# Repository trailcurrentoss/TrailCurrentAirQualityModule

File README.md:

# TrailCurrent Air Quality Module

Air quality sensor module for monitoring environmental conditions including temperature, humidity, and air quality metrics. Part of the [TrailCurrent](https://trailcurrent.com) open-source vehicle platform.

## Hardware Overview

- **Function:** Environmental monitoring module combining temperature, humidity, and air quality sensing
- **Key Features:**
  - DHT22 temperature and humidity sensor
  - Air quality sensing capability
  - Compact design suitable for integration into larger systems
  - PlatformIO-based firmware for configuration and operation

## Hardware Requirements

### Components

- **Sensors:**
  - DHT22 temperature/humidity sensor
  - Air quality sensor module

- **Connectors:**
  - JST XH 4-pin connectors for power and signal distribution

### KiCAD Library Dependencies

This project uses the consolidated [TrailCurrentKiCADLibraries](https://github.com/trailcurrentoss/TrailCurrentKiCADLibraries).

**Setup:**

```bash
# Clone the library
git clone git@github.com:trailcurrentoss/TrailCurrentKiCADLibraries.git

# Set environment variables (add to ~/.bashrc or ~/.zshrc)
export TRAILCURRENT_SYMBOL_DIR="/path/to/TrailCurrentKiCADLibraries/symbols"
export TRAILCURRENT_FOOTPRINT_DIR="/path/to/TrailCurrentKiCADLibraries/footprints"
export TRAILCURRENT_3DMODEL_DIR="/path/to/TrailCurrentKiCADLibraries/3d_models"
```

See [KICAD_ENVIRONMENT_SETUP.md](https://github.com/trailcurrentoss/TrailCurrentKiCADLibraries/blob/main/KICAD_ENVIRONMENT_SETUP.md) in the library repository for detailed setup instructions.

## Opening the Project

1. **Set up environment variables** (see Library Dependencies above)
2. **Open KiCAD:**
   ```bash
   kicad /path/to/EDA/TrailCurrentAirQualityModule/TrailCurrentAirQualityModule.kicad_pro
   ```
3. **Verify libraries load** - All symbol and footprint libraries should resolve without errors
4. **View 3D models** - Open PCB and press `Alt+3` to view the 3D visualization
   - All 3D models should load from the consolidated library path
   - Models use relative `${TRAILCURRENT_3DMODEL_DIR}` references

## Firmware

See `src/` directory for PlatformIO-based firmware.

**Setup:**
```bash
# Install PlatformIO (if not already installed)
pip install platformio

# Build firmware
pio run -d /path/to/project

# Upload to board
pio run -t upload -d /path/to/project
```

### Firmware Dependencies

This firmware depends on the following public libraries:

- **[C6SuperMiniRgbLedLibrary](https://github.com/trailcurrentoss/C6SuperMiniRgbLedLibrary)** (v0.0.1) - RGB LED status indicator driver
- **[Esp32C6OtaUpdateLibrary](https://github.com/trailcurrentoss/Esp32C6OtaUpdateLibrary)** (v0.0.1) - Over-the-air firmware update functionality
- **[Esp32C6TwaiTaskBasedLibrary](https://github.com/trailcurrentoss/Esp32C6TwaiTaskBasedLibrary)** (v0.0.3) - CAN bus communication interface
- **[Adafruit DHT sensor library](https://github.com/adafruit/DHT-sensor-library)** (v1.4.6+) - Temperature and humidity sensor

All dependencies are automatically resolved by PlatformIO during the build process.

**WiFi Credentials:**
- Firmware receives WiFi credentials via CAN Bus (ID 0x01) from the TrailCurrent system
- For standalone development/testing without the TrailCurrent system, create a `secrets.h` file in `src/`:
  ```cpp
  // Copy to src/secrets.h for local development only
  // NEVER commit this file - it's in .gitignore
  const char* ssid = "YOUR_SSID_HERE";
  const char* password = "YOUR_PASSWORD_HERE";
  ```

**Future Enhancement:** WiFi credential configuration will be fully implemented via CAN Bus protocol, allowing credentials to be distributed from the TrailCurrent system without firmware modifications.

## Manufacturing

- **PCB Files:** Ready for fabrication via standard PCB services (JLCPCB, OSH Park, etc.)
- **BOM Generation:** Export BOM from KiCAD schematic (Tools → Generate BOM)
- **JLCPCB Assembly:** This project supports automated assembly using JLCPCB
  - See [BOM_ASSEMBLY_WORKFLOW.md](https://github.com/trailcurrentoss/TrailCurrentKiCADLibraries/blob/main/BOM_ASSEMBLY_WORKFLOW.md) for detailed assembly workflow
  - Component library includes LCSC, Mouser, and DigiKey part numbers for flexible sourcing

## Documentation

- **Schematic:** EDA/TrailCurrentAirQualityModule/TrailCurrentAirQualityModule.kicad_sch
- **PCB Layout:** EDA/TrailCurrentAirQualityModule/TrailCurrentAirQualityModule.kicad_pcb

## License

MIT License - See LICENSE file for details

This is open source hardware. You are free to use, modify, and distribute these designs for personal or commercial purposes.

## Contributing

Improvements and contributions are welcome! Please submit issues or pull requests to the main repository.

## Support

For questions about:
- **KiCAD setup:** See [KICAD_ENVIRONMENT_SETUP.md](https://github.com/trailcurrentoss/TrailCurrentKiCADLibraries/blob/main/KICAD_ENVIRONMENT_SETUP.md)
- **Library consolidation:** See [CONNECTOR_CONSOLIDATION_SUMMARY.md](https://github.com/trailcurrentoss/TrailCurrentKiCADLibraries/blob/main/CONNECTOR_CONSOLIDATION_SUMMARY.md)
- **Assembly workflow:** See [BOM_ASSEMBLY_WORKFLOW.md](https://github.com/trailcurrentoss/TrailCurrentKiCADLibraries/blob/main/BOM_ASSEMBLY_WORKFLOW.md)

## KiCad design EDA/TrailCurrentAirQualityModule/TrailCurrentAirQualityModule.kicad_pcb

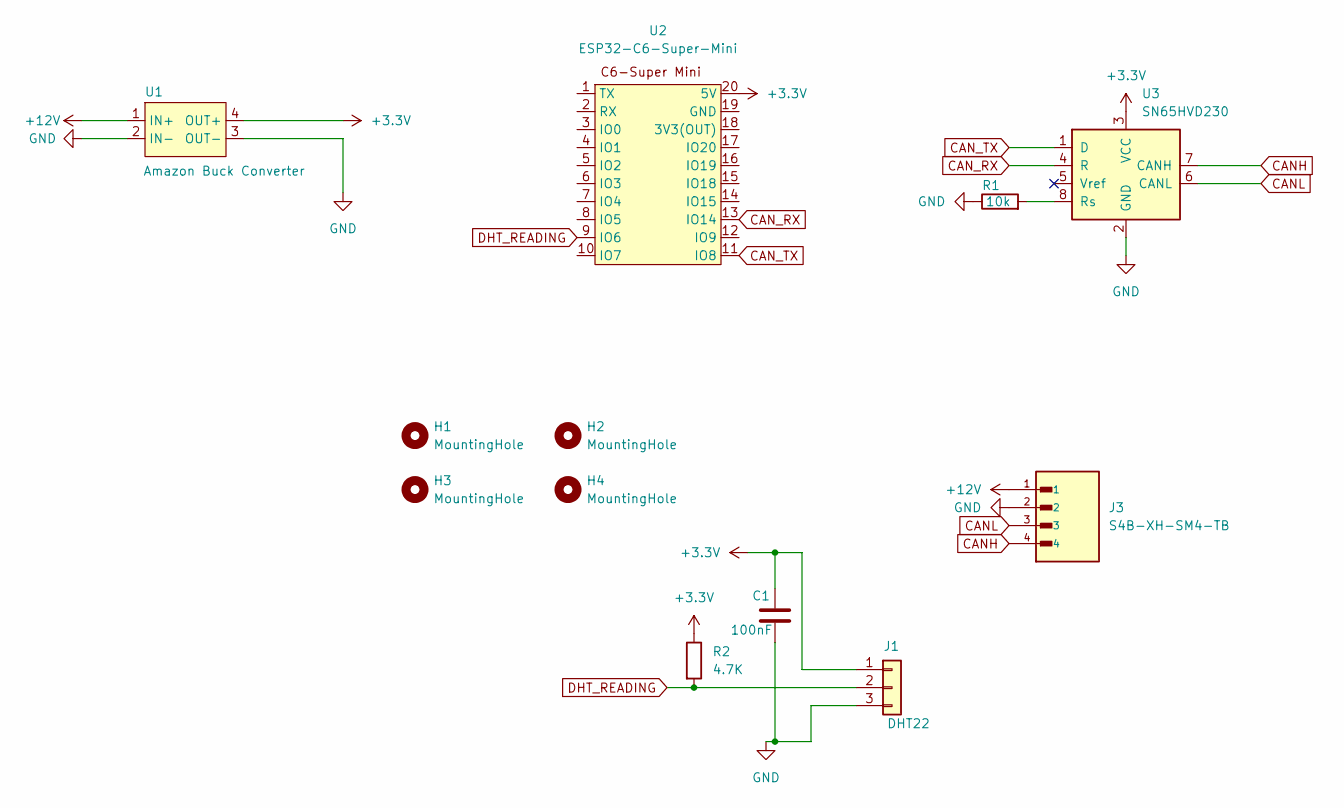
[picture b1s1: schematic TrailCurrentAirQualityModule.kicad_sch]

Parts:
C1: 100nF; C_1206_3216Metric_Pad1.33x1.80mm_HandSolder
H1, H2, H3, H4: MountingHole; MountingHole_2.5mm
J1: DHT22; DHT22_Module
J3: S4B-XH-SM4-TB; JST_S4B-XH-SM4-TB; PARTREV NA; LCSC C161861
R1: 10k; R_1206_3216Metric_Pad1.30x1.75mm_HandSolder
R2: 4.7K; C_1206_3216Metric_Pad1.33x1.80mm_HandSolder
U1: Amazon Buck Converter; AmazonBuckConverter
U2: ESP32-C6-Super-Mini
U3: SN65HVD230; SOIC-8_3.9x4.9mm_P1.27mm

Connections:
+3.3V: C1.1, J1.1, R2.1, U1.4 (OUT+), U2.20 (5V), U3.3 (VCC)
+12V: J3.1, U1.1 (IN+)
CANH: J3.4, U3.7 (CANH)
CANL: J3.3, U3.6 (CANL)
CAN_RX: U2.13 (IO14), U3.4 (R)
CAN_TX: U2.11 (IO8), U3.1 (D)
DHT_READING: J1.2, R2.2, U2.9 (IO6)
GND: C1.2, J1.3, J3.2, R1.1, U1.2 (IN-), U1.3 (OUT-), U3.2 (GND)
unnamed: R1.2, U3.8 (Rs)

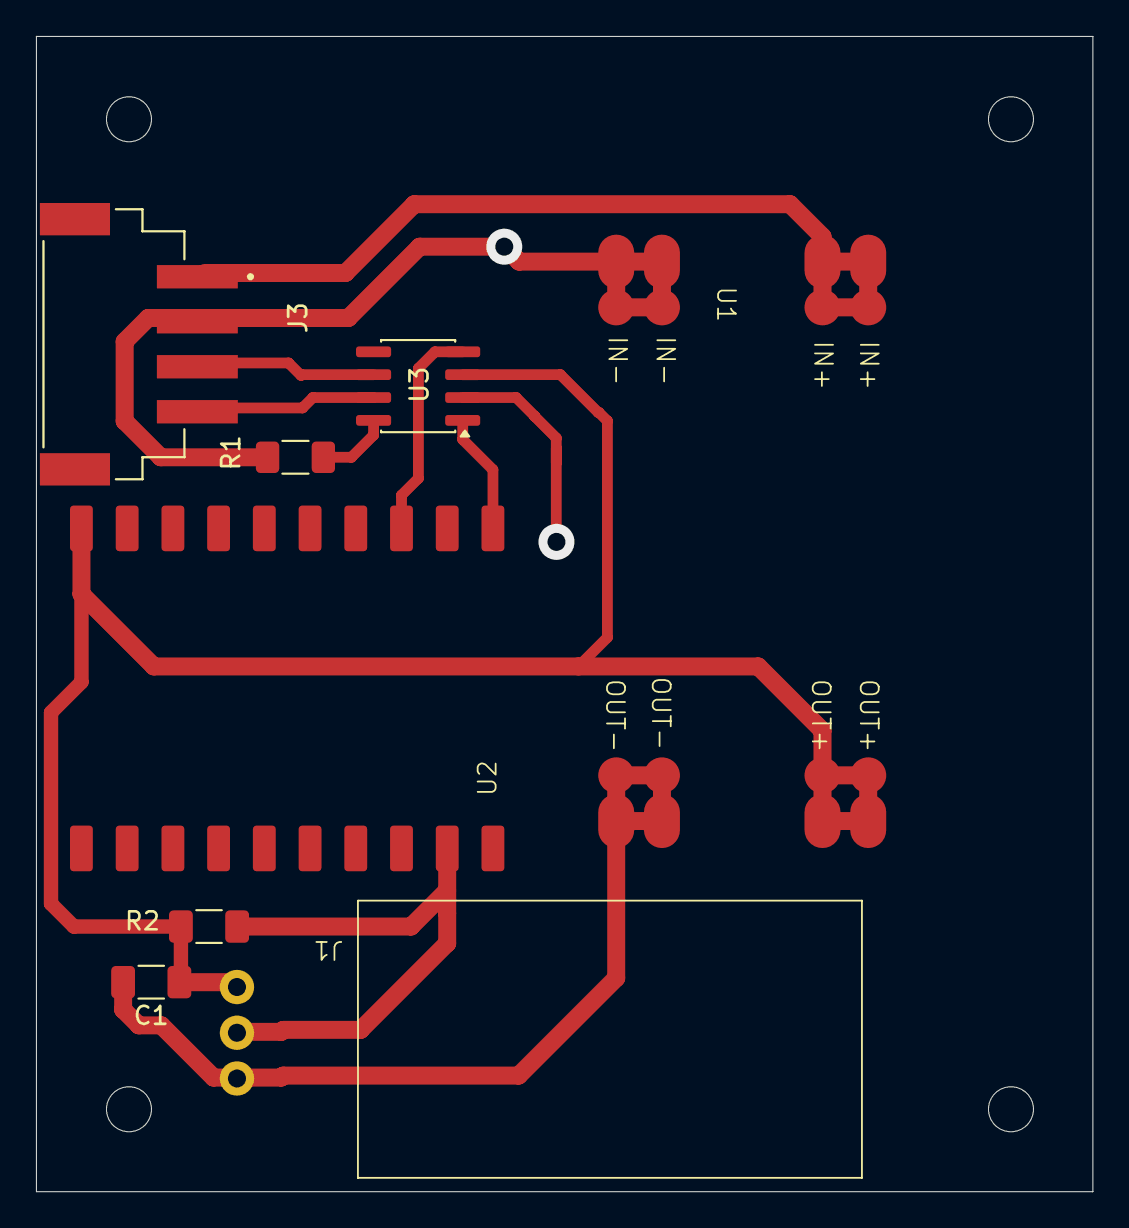
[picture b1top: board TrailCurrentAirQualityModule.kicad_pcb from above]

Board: 2 copper layers, 58.7 x 64.2 mm, 12 parts (0 on the bottom side), 9 nets.

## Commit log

2026-02-12 Initial commit: Clean migration to public Codeberg repository
    This is a fresh start on Codeberg with all security and configuration
    issues addressed:
    Security fixes:
    - Removed all git history (fresh start)
    - No personal paths or credentials exposed
    - All WiFi secrets in .gitignore (using secrets.h.example pattern)
2026-02-12 Update Codeberg URLs to trailcurrentopensource org
2026-02-14 Updating license file
2026-02-14 Update docs: replace Codeberg URLs with GitHub references
2026-02-22 Updated to remove secrets and get them from CAD
2026-02-23 Add trailcurrent.com link to README
